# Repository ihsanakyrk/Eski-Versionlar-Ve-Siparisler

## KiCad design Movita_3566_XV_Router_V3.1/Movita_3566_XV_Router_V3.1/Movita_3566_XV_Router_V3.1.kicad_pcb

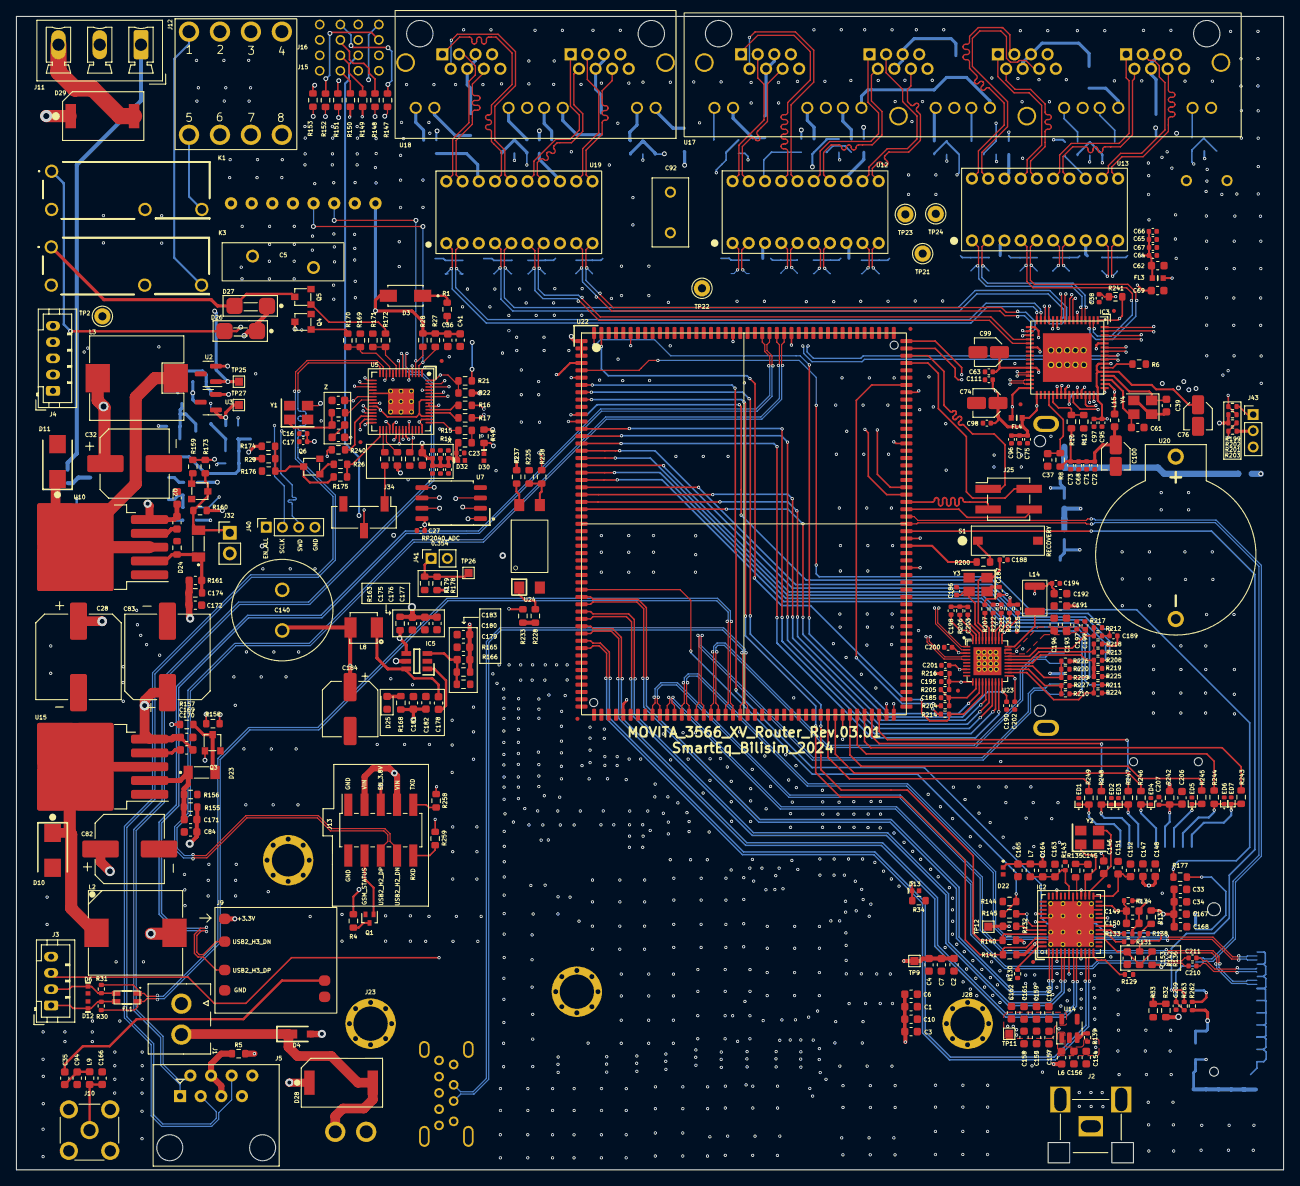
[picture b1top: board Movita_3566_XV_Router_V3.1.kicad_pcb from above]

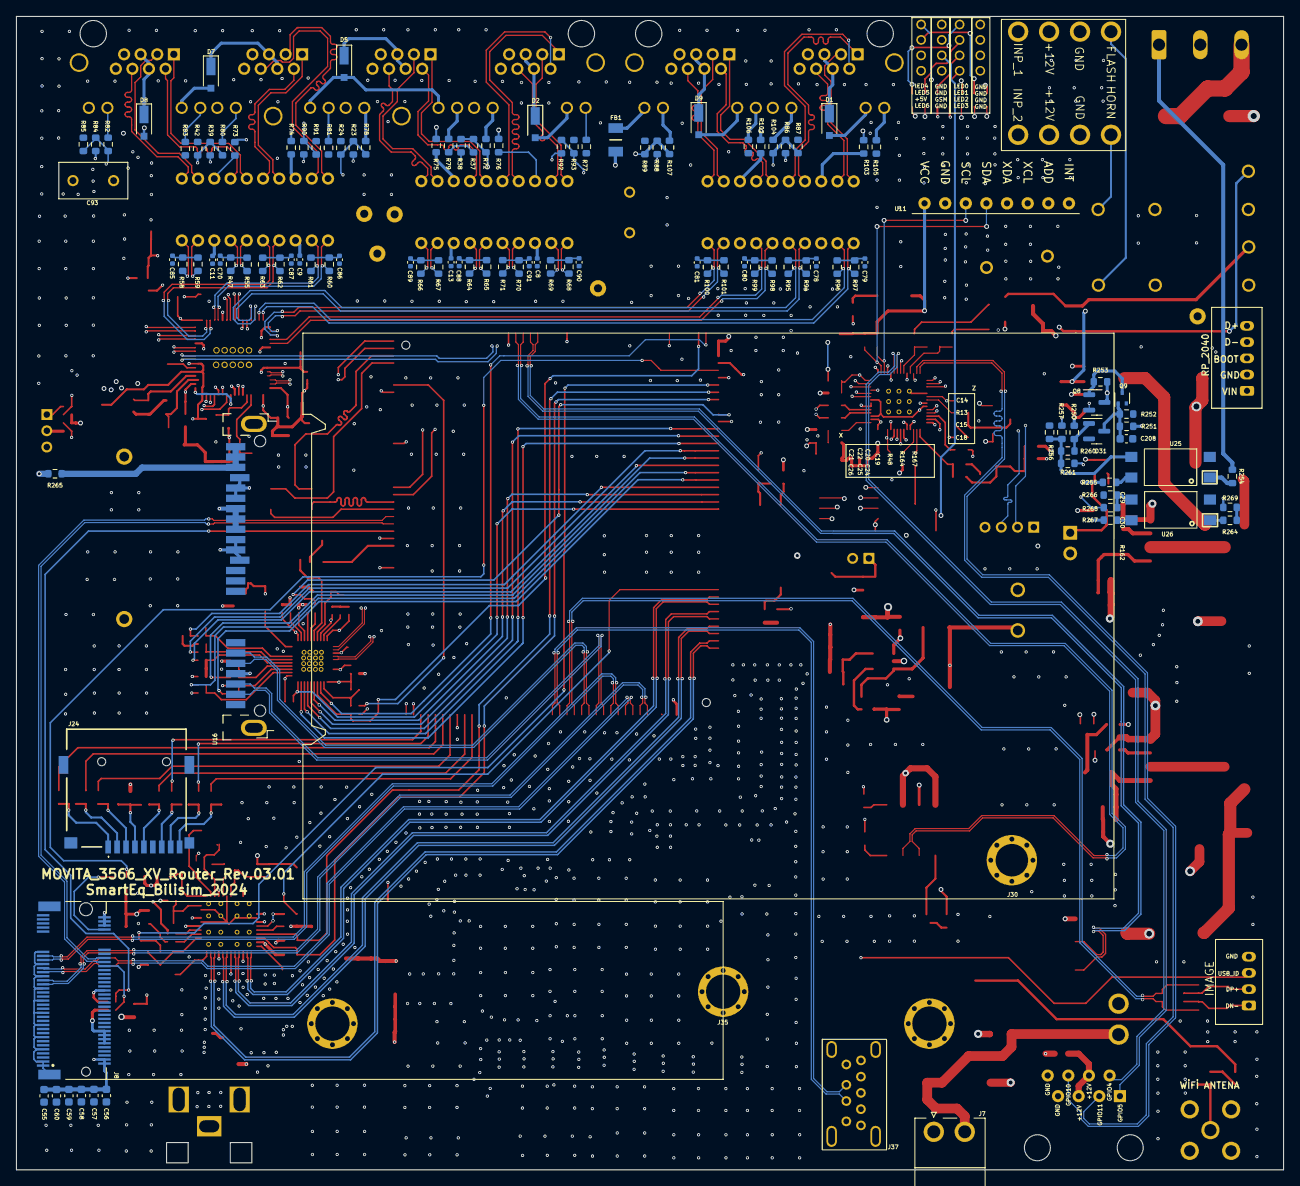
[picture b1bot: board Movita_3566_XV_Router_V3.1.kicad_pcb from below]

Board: 6 copper layers, 156.0 x 142.0 mm, 474 parts (118 on the bottom side), 347 nets.

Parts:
C1, C2, C3, C34, C36, C41, C55, C56, C57, C58, C59, C60, C147, C148, C150, C152, C156, C157, C158, C159, C160, C161, C162, C167, C168, C178, C182, C183, C208: 100nF; C_0603_1608Metric
C4, C6, C33, C149, C154, C191, C193, C196: 4.7uF; C_0603_1608Metric
C5: ERZ-V14D101; ERZV14D101
C7, C10, C37, C151, C155, C175, C176, C177, C192, C206: 10uF; C_0603_1608Metric
C8, C9, C11, C13, C16, C17, C20, C21, C22, C23, C24, C25, C26, C27, C38, C63, C64, C65, C66, C67, C68, C71, C72, C73, C75, C77, C95, C96, C97, C98, C111, C194, C195, C197, C198, C199, C200, C201, C202, C203, C207, C210, C211: 100nF; C_0402_1005Metric
C14, C15: 27pF; C_0603_1608Metric
C18, C19: 1uF; C_0603_1608Metric
C28, C83: 220uF/50V; C_Elec_10x10.2
C29, C30, C84, C169, C170, C172: 1uF/50V; C_0603_1608Metric
C32, C82: 330uF/25V; C_Elec_8x10.2
C35, C94, C166: 10pF; C_0603_1608Metric
C39, C61: 33pF; C_0603_1608Metric
C62, C69, C180, C181: 22uF; C_0603_1608Metric
C70, C78, C79, C80, C81, C85, C86, C87, C88, C89, C90, C91, C187, C189, C190: DNP; C_0402_1005Metric
C74, C76, C99, C100: 10uF; C_Elec_3x5.4
C92, C93: 1000PF 2KV; S102K33Y5PP63K5R
C140: 5.5V 0.22F; SuperCapacitor
C145, C146, C179: 22pF; C_0603_1608Metric
C153: 10nF; C_0603_1608Metric
C163: 100pF; C_0603_1608Metric
C164: DNP; C_0603_1608Metric
C165: 220pF; C_0603_1608Metric
C171, C174: 330nF; C_0603_1608Metric
C184: 220uF; CP_Elec_6.3x7.7
C185: 10nF; C_0402_1005Metric
C186, C188: 15pF; C_0402_1005Metric
C209: 100nF X7R 16V; C_0402_1005Metric
D1, D2, D4, D5, D7, D8, D9: 2SS100L-W; 2SS100LW
D3: SS14; DIOM4325X250N
D6, D12, D13, D30, D32: ESD5341N
D10, D11: SS54B
D22: ESD5451N
D23, D24: LL4148
D25: LED_GREEN; LED_0603_1608Metric
D26, D27: MRA4007T3G
D28, D29: S6MC
D31: BAT54; SOT-23
ED1, ED2, ED3, ED4, ED5, ED6, ED7: ESD5341N
FB1: YI321611U101-4R0T; BEADC3216X130N
FID1, FID2, FID5, FID6, FID7, FID8, FID9, FID10, FID11, FID12: DNP; Fiducial_0.5mm_Mask1mm
FL1: APCW3216-900P2T; DLW31SH222SQ2L
FL3, FL4: BLM18PG121SN1D; BLM18AG102BH1D
IC2: MS1836S_QFN48-7x7; QFN-48-1EP_7x7mm_P0.5mm_EP5.6x5.6mm
IC3: RTL8309N
IC5: SY8113B
J1: KF2EDGH-3.81-2P- Vertical; KF2EDGH-3.81-2P-Vertical
J2: DNP; AV_CON
J3: JST_PH_B4B-PH-K_1x04_P2.00mm_Vertical
J4: JST_PH_B5B-PH-K_1x05_P2.00mm_Vertical
J5: RJ45; RJ45_Amphenol_54602-x08_Horizontal
J7: KF2EDGH-3.81-2P- Right Angle; KF2EDGH-3.81-2P
J8: APCI0079-P002A J8900 M.2 M Key
J9: RTL8188EU
J10: SMA Connetor_inner_pin; SMA_Connector_inner_pin_right_angle
J11: KF2EDGR-Y-5.08-3P-Right Angle
J12: KF2EDGH-3.81_8P-Right Angle; KF2EDGH-3.81_8P
J13: MALE SMD Pin Header; PinSocket_2x05_P2.00mm_Vertical_SMD
J15, J16: LED_4_Block_Right Angle; LED_4_Block
J23, J28, J30: M3x*0.5 L=6; Screw Terminal Shinbo
J24: TF-CARD H1.8
J25: DNP; PinHeader_2x02_P2.54mm_Vertical_SMD
J32: DNP; PinHeader_1x02_P2.54mm_Vertical
J34: FEMALE SMD Pin Header; PinSocket_1x03_P2.54mm_Vertical_SMD_Pin1Left
J35: M3x*0.5 L=3; Screw Terminal Shinbo
J37: DNP; CP-USB-3015
J40: DNP; PinSocket_1x04_P2.00mm_Vertical
J41: DNP; PinSocket_1x02_P2.00mm_Vertical
J43: MALE Through Hole Pin Header; PinHeader_1x03_P2.00mm_Vertical
K1, K3: HF46F_5-HS1; HF46F5HS1
L2, L3: HX CYA1050-47UH; L_Bourns_SRR1208_12.7x12.7mm
L6: UPZ1608E101-3R0TF; L_0603_1608Metric
L7: MLI1608F-1R2KT; L_0603_1608Metric
L8: HA42-4R7MT; Inductor_0402_4.7uH
L9: SDCL1608C2N7STDF; L_0603_1608Metric
L14: AWL3225FP2R2MTF
L15: CBW160808U101T; L_0603_1608Metric
Q1: DTC043ZEBTL; SOT-416
Q2, Q3, Q4, Q5, Q6: MMBT2222ALT1G
Q8: DMG2305UX; SOT-23
Q9: DMG1012T; SOT-523
R1: 150R; R_0603_1608Metric
R4, R140, R141, R228, R264: 2.2K; R_0603_1608Metric
R5, R29, R241, R242: 0R; R_0603_1608Metric
R6, R8: 2.49K; R_0603_1608Metric
R10, R13, R21, R23, R37, R39, R48, R72, R77, R78, R79, R80, R81, R82, R83, R84, R87, R88, R104, R105, R106, R107, R132, R145, R170, R172, R233, R238, R250, R251, R257, R268, R269: 1K; R_0603_1608Metric
R12, R22, R24, R26, R38, R42, R47, R55, R58, R59, R60, R61, R62, R63, R64, R65, R66, R67, R68, R69, R70, R71, R85, R86, R89, R90, R91, R92, R93, R94, R95, R96, R97, R98, R99, R100, R101, R163, R167, R173, R174, R175, R176, R177, R240, R258, R259, R260, R261, R265: DNP; R_0603_1608Metric
R14: 200R; R_0603_1608Metric
R15: 1R; R_0603_1608Metric
R16, R17: 27R; R_0603_1608Metric
R27, R28, R32, R33, R34: 4.7K; R_0603_1608Metric
R30, R31: 2.2R; R_0402_1005Metric
R49, R136, R137, R149, R150, R155, R158, R159, R164, R169, R171, R235, R256, R266: 10K; R_0603_1608Metric
R73, R74, R75, R76, R102, R103: 75R; R_0603_1608Metric
R129, R138, R205, R225, R226: DNP; R_0402_1005Metric
R130, R199, R201, R262: 10K; R_0402_1005Metric
R131, R133, R134, R139, R204, R216: 0R; R_0402_1005Metric
R135: 330R; R_0603_1608Metric
R142, R243, R244, R245, R246, R247, R248, R249: 22R; R_0603_1608Metric
R143: 75R; R_0402_1005Metric
R144, R252, R253: 100K; R_0603_1608Metric
R147, R148, R151, R152, R153: 220R; R_0603_1608Metric
R156, R254: 3.3K; R_0603_1608Metric
R157, R160: 470R; R_0603_1608Metric
R161: 15K; R_0603_1608Metric
R162: 1.6K; R_0603_1608Metric
R165: 232K; R_0603_1608Metric
R166: 51K; R_0603_1608Metric
R168, R178: 2K; R_0603_1608Metric
R179: 180R; R_0603_1608Metric
R200: 100R; R_0603_1608Metric
R202, R203: 10R; R_0402_1005Metric
R206: 2.49K; R_0402_1005Metric
R207, R208, R209, R210, R211, R212, R213: 22R; R_0402_1005Metric
R214: 1.5K; R_0402_1005Metric
R215, R217, R218, R219, R220, R221, R222, R223, R224, R227: 4.7K; R_0402_1005Metric
R237, R255, R267: 33R; R_0603_1608Metric
R263: 1K; R_0402_1005Metric
S1: TS-1101-C-W
TP2, TP21, TP22, TP23, TP24: DNP; Pin_D1.0mm_L10.0mm
TP9, TP11, TP12, TP25, TP26, TP27: DNP; TestPoint_Pad_1.0x1.0mm
U2, U3: TLV76033DBZT; SOT-23
U5: RP2040; RP2040-QFN-56
U7: W25Q128JVSIQ; SOIC-8_5.23x5.23mm_P1.27mm
U10, U15: XL4015; TO-263-5_TabPin3
U11: DNP; module_mpu6050
U12, U13, U19: TF-218DG; RJ45_Transformer_2_Port
U14: RT9013-12GB; SOT-23-5
U16: SAF-8ASC-2132M; SATA_Connector_5622-1200-ML
U17: RJ45-4-Block; 4_Block_RJ45
U18: RJ45-2-Block; 2_Block_RJ45
U20: BS-2; BS-02-A1AJ010
U22: CM3566
U23: RTL8211F-CG
U24, U25, U26: PC817C; PC817
Y1: CF4012M00020001; Crystal_SMD_3225-4Pin_3.2x2.5mm
Y2: TAXM27M4RFBCCT2T; Crystal_SMD_3225-4Pin_3.2x2.5mm
Y3, Y4: X322525MSB4SI; Crystal_SMD_3225-4Pin_3.2x2.5mm

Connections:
3.3V_Sensor: C36.1, C41.1, D3.A, R27.1, R28.2, TP25.1, U2.1 (OUT), U11.1 (VCC)
+1V1: C16.1, C17.1, C18.1, U5.23 (DVDD), U5.45 (VREG_VOUT), U5.50 (DVDD)
/4 Port RJ45 and Transformer/+3.3V: C2.1, C4.1, C7.1, C55.1, C56.1, C57.1, C58.1, C59.1, C60.1, C140.1, C179.2, C180.2, C181.2, C182.2, C183.2, C184.1, C191.1, FB1.1, FL3.1, J8.2, J8.4, J8.12, J8.14, J8.16, J8.18, J8.70, J8.72, J8.74, J9.1, L6.1, L8.2, R29.2, R165.1, R168.1, R178.1, R199.1, R201.1, R216.1, R237.1, R242.2, R262.1, R267.1, TP9.1, U22.1, U22.2, U22.3
/4 Port RJ45 and Transformer/LED0: IC3.38 (P0LED/DIS_EEE), R37.1, R38.2, R72.1
/4 Port RJ45 and Transformer/LED1: IC3.39 (P1LED/LED_MODE[1]), R23.1, R24.2, R78.2
/4 Port RJ45 and Transformer/LED2: IC3.40 (P2LED/LED_MODE[2]), R39.1, R42.2, R80.2
/4 Port RJ45 and Transformer/LED3: IC3.42 (P3LED/RMAMODE), R82.2, R84.1, R85.2
/4 Port RJ45 and Transformer/LED4: IC3.43 (P4LED/UNKOWN_MULTI), R86.1, R87.2, R104.2
/4 Port RJ45 and Transformer/LED5: IC3.44 (P5LED/DIS_RST_BLNK), R88.1, R89.2, R107.2
/4 Port RJ45 and Transformer/RXI_0_N: IC3.57 (RXIN0), R71.2, U12.5
/4 Port RJ45 and Transformer/RXI_0_P: IC3.56 (RXIP0), R70.2, U12.4
/4 Port RJ45 and Transformer/RXI_1_N: IC3.63 (RXIN1), R64.2, U12.7
/4 Port RJ45 and Transformer/RXI_1_P: IC3.64 (RXIP1), R65.2, U12.6
/4 Port RJ45 and Transformer/RXI_2_N: IC3.3 (RXIN2), R63.2, U13.5
/4 Port RJ45 and Transformer/RXI_2_P: IC3.2 (RXIP2), R62.2, U13.4
/4 Port RJ45 and Transformer/RXI_3_N: IC3.9 (RXIN3), R47.2, U13.7
/4 Port RJ45 and Transformer/RXI_3_P: IC3.10 (RXIP3), R55.2, U13.6
/4 Port RJ45 and Transformer/RXI_4_N: IC3.14 (RXIN4), R95.2, U19.5
/4 Port RJ45 and Transformer/RXI_4_P: IC3.13 (RXIP4), R94.2, U19.4
/4 Port RJ45 and Transformer/RXI_5_N: IC3.20 (RXIN5), R99.2, U19.7
/4 Port RJ45 and Transformer/RXI_5_P: IC3.21 (RXIP5), R98.2, U19.6
/4 Port RJ45 and Transformer/TXO_0_N: IC3.58 (TXON0), R69.2, U12.2
/4 Port RJ45 and Transformer/TXO_0_P: IC3.59 (TXOP0), R68.2, U12.1
/4 Port RJ45 and Transformer/TXO_1_N: IC3.62 (TXON1), R66.2, U12.10
/4 Port RJ45 and Transformer/TXO_1_P: IC3.61 (TXOP1), R67.2, U12.9
/4 Port RJ45 and Transformer/TXO_2_N: IC3.4 (TXON2), R61.2, U13.2
/4 Port RJ45 and Transformer/TXO_2_P: IC3.5 (TXOP2), R60.2, U13.1
/4 Port RJ45 and Transformer/TXO_3_N: IC3.8 (TXON3), R58.2, U13.10
/4 Port RJ45 and Transformer/TXO_3_P: IC3.7 (TXOP3), R59.2, U13.9
/4 Port RJ45 and Transformer/TXO_4_N: IC3.15 (TXON4), R96.2, U19.2
/4 Port RJ45 and Transformer/TXO_4_P: IC3.16 (TXOP4), R97.2, U19.1
/4 Port RJ45 and Transformer/TXO_5_N: IC3.19 (TXON5), R100.2, U19.10
/4 Port RJ45 and Transformer/TXO_5_P: IC3.18 (TXOP5), R101.2, U19.9
/+12V: C32.1, C172.2, C174.2, C175.2, C176.2, C177.2, D1.2, D2.2, D4.2, D5.2, D7.2, D8.2, D9.2, IC5.5 (IN), J12.3, J12.7, L3.2, R5.1, R161.1, R163.1, R265.2, TP2.1, U17.P1_L_Led+, U17.P2_L_Led+, U17.P3_L_Led+, U17.P4_L_Led+, U18.P1_L_Led+, U18.P2_L_Led+
/CM3566/GMAC1_MCLKINOUT_M0: C187.1, R207.1, U22.11
/CM3566/GMAC1_MDC_M0: U22.186, U23.13 (MDC)
/CM3566/GMAC1_MDIO_M0: R214.2, U22.185, U23.14 (MDIO)
/CM3566/GMAC1_RXCLK_M0: C189.1, R212.1, U22.21
/CM3566/GMAC1_RXD0_M0: R208.1, U22.18
/CM3566/GMAC1_RXD1_M0: R209.1, U22.17
/CM3566/GMAC1_RXD2_M0: R210.1, U22.20
/CM3566/GMAC1_RXD3_M0: R211.1, U22.19
/CM3566/GMAC1_RXDV_CRS_M0: R213.1, U22.16
/CM3566/GMAC1_TXCLK_M0: C190.1, U22.24, U23.20 (TXC)
/CM3566/GMAC1_TXD0_M0: U22.13, U23.18 (TXD0)
/CM3566/GMAC1_TXD1_M0: U22.14, U23.17 (TXD1)
/CM3566/GMAC1_TXD2_M0: U22.22, U23.16 (TXD2)
/CM3566/GMAC1_TXD3_M0: U22.23, U23.15 (TXD3)
/CM3566/GMAC1_TXEN_M0: U22.15, U23.19 (TXCTL)
/CM3566/HDMI_TX_HPDIN: R144.1, R145.2, U22.35
/CM3566/LED0/CFG_EXT: R223.1, U23.32 (LED0/CFG_EXT)
/CM3566/LED1/CFG_LDO0: R221.2, U23.33 (LED1/CFG_LDO0_)
/CM3566/LED2/CFG_LDO1: R222.2, U23.34 (LED2/CFG_LDO1)
/CM3566/PCIE20_CLKREQn_M2: J8.52, U22.120
/CM3566/PCIE20_PERSTn_M2: R263.1, U22.118
/CM3566/PCIE20_REFCLKN: J8.53, U22.65
/CM3566/PCIE20_REFCLKP: J8.55, U22.64
/CM3566/PCIE20_RXN: J8.41, U22.61
/CM3566/PCIE20_RXP: J8.43, U22.60
/CM3566/PCIE20_TXN: C210.1, U22.62
/CM3566/PCIE20_TXP: C211.1, U22.63
/CM3566/PCIE20_WAKEn_M2: J8.54, U22.119
/CM3566/PHY0_XTALIN: C188.1, U23.36 (XTAL_IN), Y3.1 (XIN)
/CM3566/PHY0_XTALOUT: C186.1, U23.37 (XTAL_OUT/EXT_CLK), Y3.3 (XOUT)
/CM3566/PHY1_MDI0+: IC3.28 (TXOP7), U23.1 (MDI[0]+)
/CM3566/PHY1_MDI0-: IC3.29 (TXON7), U23.2 (MDI[0]-)
/CM3566/PHY1_MDI1+: IC3.31 (RXIP7), U23.4 (MDI[1]+)
/CM3566/PHY1_MDI1-: IC3.30 (RXIN7), U23.5 (MDI[1]-)
/CM3566/PHY-Reset: C185.1, R204.2, R205.1, U23.12 (PHYRSTB)
/CM3566/PHY_CLKOUT125: R207.2, U23.35 (CLKOUT)
/CM3566/PHY_RXCLK/PHYAD1: R212.2, R217.2, U23.27 (RXC/PHYAD1)
/CM3566/PHY_RXD0/RXDLY: R208.2, R219.2, R225.1, U23.25 (RXD0/RXDLY)
/CM3566/PHY_RXD1/TXDLY: R209.2, R220.2, R226.1, U23.24 (RXD1/TXDLY)
/CM3566/PHY_RXD2/PLLOFF: R210.2, R227.1, U23.23 (RXD2/PLLOFF)
/CM3566/PHY_RXD3/PHYAD0: R211.2, R224.1, U23.22 (RXD3/PHYAD0)
/CM3566/PHY_RXDV/PHYAD2: R213.2, R218.2, U23.26 (RXCTL/PHYAD2)
/CM3566/PMIC_32KOUT_SOC: R177.1, U22.5
/CM3566/REG_OUT: L14.1, U23.30 (REG_OUT)
/CM3566/RSET: R206.2, U23.39 (RSET)
/CM3566/SARADC_VIN0_KEY/RECOVERY: R200.1, U22.116
/CM3566/SATA0_RXN: U16.S5 (RX-), U22.69
/CM3566/SATA0_RXP: U16.S6 (RX+), U22.68
/CM3566/SATA0_TXN: U16.S3 (TX-), U22.67
/CM3566/SATA0_TXP: U16.S2 (TX+), U22.66
/CM3566/SDMMC0_CLK: R246.1, U22.85
/CM3566/SDMMC0_CMD: R245.1, U22.87
/CM3566/SDMMC0_D0: R247.1, U22.91
/CM3566/SDMMC0_D1: R248.1, U22.90
/CM3566/SDMMC0_D2: R243.1, U22.89
/CM3566/SDMMC0_D3: R244.1, U22.88
/CM3566/SDMMC0_DET_L: R249.1, U22.84
/CM3566/SPI3_CLK_M1: R204.1, U22.138
/CM3566/SPI3_MOSI_M1: R215.1, U22.137, U23.31 (INTB/PMEB)
/CM3566/UART2_RX_M0_DEBUG: R201.2, R203.2, U22.143
/CM3566/UART2_TX_M0_DEBUG: R199.2, R202.2, U22.144
/CM3566/UART3_RX_M0: J25.4, U22.121
/CM3566/UART3_TX_M0: J25.3, U22.122
/CM3566/UART4_RX_M0: R259.2, U5.27 (GPIO16), U22.123
/CM3566/UART4_TX_M0: R258.2, U5.28 (GPIO17), U22.124
/CM3566/UART5_RX_M1: J25.2, U22.141
/CM3566/UART5_TX_M1: J25.1, U22.142
/CM3566/USB2_HOST2_DN: J13.8, U22.160
/CM3566/USB2_HOST2_DP: J13.6, U22.161
/CM3566/USB2_HOST3_DN: J9.2, U22.163
/CM3566/USB2_HOST3_DP: J9.3, U22.162
/CM3566/USB3_HOST1_DN: J37.2 (D-), U22.73
/CM3566/USB3_HOST1_DP: J37.3 (D+), U22.72
/CM3566/USB3_OTG0_DN: FL1.4, R30.1, U22.70
/CM3566/USB3_OTG0_DP: FL1.1, R31.1, U22.71
/CM3566/USB3_OTG0_ID: D13.1, J3.3, R34.2, U22.92
/CM3566/USB3_OTG0_VBUSDET: R32.2, R33.1, U22.93
/CM3566/VCC3V3_LAN: C193.1, C195.1, C196.1, C197.1, C198.1, C199.1, R205.2, R214.1, R215.2, R216.2, R223.2, R224.2, R225.2, R226.2, R227.2, U23.11 (AVDD33_2), U23.28 (DVDD_RG), U23.29 (DVDD33), U23.40 (AVDD33_1)
/CM3566/VDD10_EPHY: C192.1, C194.1, C200.1, C201.1, C202.1, C203.1, L14.2, U23.3 (AVDD10_3), U23.8 (AVDD10_2), U23.21 (DVDD10), U23.38 (AVDD10_1)
/CM3566/VDD_5V: C1.1, C3.1, C6.1, C10.1, C82.1, C84.2, C171.2, D26.1 (K), D27.1 (K), J16.6, J37.1 (VBUS), K1.2 (COIL_2), K3.2 (COIL_2), L2.2, R32.1, R155.1, R174.2, U16.P7 (VCC5), U16.P8 (VCC5), U16.P9 (VCC5)
/CM3566/VRTC: R1.2, U20.1 (+), U22.4
/EC25_Sim/GSM_LED: J16.5, R4.2
/EC25_Sim/GSM_STATUS: J13.4, Q1.1 (B)
/HDMI_CVBS/CVideo_OUT: C164.2, C165.1, D22.1, J2.1, J2.2, L7.2
/HDMI_CVBS/DAC_R: C163.1, C164.1, IC2.31 (AV_OUT), L7.1, R143.2
/HDMI_CVBS/HDMITX_CEC_M0: R142.1, U22.7
/HDMI_CVBS/HDMI_RX_HPD: IC2.43 (HDMIRX_HPD), R145.1
/HDMI_CVBS/HDMI_TX0N_PORT: IC2.4 (HDMI_RX0N), U22.38
/HDMI_CVBS/HDMI_TX0P_PORT: IC2.5 (HDMI_RX0P), U22.39
/HDMI_CVBS/HDMI_TX1N_PORT: IC2.7 (HDMI_RX1N), U22.40
/HDMI_CVBS/HDMI_TX1P_PORT: IC2.8 (HDMI_RX1P), U22.41
/HDMI_CVBS/HDMI_TX2N_PORT: IC2.10 (HDMI_RX2N), U22.42
/HDMI_CVBS/HDMI_TX2P_PORT: IC2.11 (HDMI_RX2P), U22.43
/HDMI_CVBS/HDMI_TXCLKN_PORT: IC2.1 (HDMI_RXCN), U22.36
/HDMI_CVBS/HDMI_TXCLKP_PORT: IC2.2 (HDMI_RXCP), U22.37
/HDMI_CVBS/P/N_SEL: R131.1, R137.2, R138.1
/HDMI_CVBS/RSTn: C153.1, IC2.15 (RSTn), R136.1, R142.2
/HDMI_CVBS/RXDDC_SCL: IC2.46 (RXDDC_SCL), R141.1, U22.9
/HDMI_CVBS/RXDDC_SDA: IC2.45 (RXDDC_SDA), R140.1, U22.8
/HDMI_CVBS/RX_DET: IC2.44 (HDMIRX_DET), R132.2
/HDMI_CVBS/VDD10_EPHY: C155.1, C157.1, C158.1, C159.1, C160.1, C161.1, C162.1, IC2.3 (AVDD12), IC2.9 (AVDD12_1), IC2.20 (DVDD12), IC2.40 (DVDD12_1), TP11.1, U14.5 (OUT)
/HDMI_CVBS/XTAL1: C145.1, IC2.27 (XTOUT), Y2.1
/HDMI_CVBS/XTAL2: C146.1, IC2.26 (XTIN), Y2.3
/IO Connector/FLASH: J12.1, K3.4 (COM)
/IO Connector/GP3_A: J34.1, R167.2
/IO Connector/HORN: J12.5, K1.4 (COM)
/IO Connector/SWCLK: J40.2, U5.24 (SWCLK)
/IO Connector/SWD: J40.3, U5.25 (SWD)
/Power Unit/+3V3_Mini: C19.1, C20.1, C21.1, C22.1, C23.1, C24.1, C25.1, C26.1, C27.1, D32.1, Q8.2 (S), R14.1, R22.1, R157.1, R160.1, U5.1 (IOVDD), U5.10 (IOVDD), U5.22 (IOVDD), U5.33 (IOVDD), U5.42 (IOVDD), U5.44 (VREG_IN), U5.48 (USB_VDD), U5.49 (IOVDD), U7.8 (VCC)
/Power Unit/IGN_LOGIC: R256.1, R257.1, R260.1, R261.1, U25.3 (E)
/Power Unit/IGN_V: Q8.3 (D), R250.2, R253.2, R255.1, TP27.1, U3.1 (OUT)
/Power Unit/MCU_Power_EN: Q6.3 (C), R29.1, R174.1, R175.1, R176.1
/RP2040/GPIO0: R27.2, U5.2 (GPIO0), U11.4 (SDA)
/RP2040/GPIO1: R28.1, U5.3 (GPIO1), U11.3 (SCL)
/RP2040/GPIO2: R251.1, R261.2, U5.4 (GPIO2)
/RP2040/GPIO3: R257.2, U5.5 (GPIO3)
/RP2040/GPIO4: J5.2, U5.6 (GPIO4)
/RP2040/GPIO5: J5.1, U5.7 (GPIO5)
/RP2040/GPIO6: R147.1, U5.8 (GPIO6)
/RP2040/GPIO7: R171.1, R172.1, U5.9 (GPIO7)
/RP2040/GPIO8: R169.1, R170.1, U5.11 (GPIO8)
/RP2040/GPIO9: R148.1, U5.12 (GPIO9)
/RP2040/GPIO10: J5.6, U5.13 (GPIO10)
/RP2040/GPIO11: J5.3, U5.14 (GPIO11)
/RP2040/GPIO12: R151.1, U5.15 (GPIO12)
/RP2040/GPIO13: R152.1, U5.16 (GPIO13)
/RP2040/GPIO14: R153.1, U5.17 (GPIO14)
/RP2040/GPIO18: R26.1, R175.2, U5.29 (GPIO18)
/RP2040/GPIO19: R167.1, U5.30 (GPIO19)
/RP2040/GPIO20: R164.2, U5.31 (GPIO20)
/RP2040/GPIO21: J13.5, U5.32 (GPIO21)
/RP2040/GPIO22: R158.1, U5.34 (GPIO22)
/RP2040/GPIO23: R159.1, R173.1, U5.35 (GPIO23)
/RP2040/GPIO24: R268.2, U5.36 (GPIO24)
/RP2040/GPIO25: R238.2, U5.37 (GPIO25)
/RP2040/GPIO26_ADC0: J41.1, R178.2, R179.1, TP26.1, U5.38 (GPIO26_ADC0)
/RP2040/GPIO27_ADC1: D30.1, R48.1, R49.2, U5.39 (GPIO27_ADC1)
/RP2040/QSPI_SCLK: U5.52 (QSPI_SCLK), U7.6 (CLK)
/RP2040/QSPI_SD0: U5.53 (QSPI_SD0), U7.5 (DI(IO0))
/RP2040/QSPI_SD1: U5.55 (QSPI_SD1), U7.2 (DO(IO1))
/RP2040/QSPI_SD2: U5.54 (QSPI_SD2), U7.3 (IO2)
/RP2040/QSPI_SD3: U5.51 (QSPI_SD3), U7.7 (IO3)
/RP2040/QSPI_SS: R21.1, R22.2, U5.56 (QSPI_SS), U7.1 (~CS)
/RP2040/RUN: J34.2, R240.2
/RP2040/USB_D+_RP2040: J4.5, R16.1
/RP2040/USB_D-_RP2040: J4.4, R17.1
/RP2040/USB_D_N: R17.2, U5.46 (USB_DM)
/RP2040/USB_D_P: R16.2, U5.47 (USB_DP)
/RP2040/XIN: C14.1, U5.20 (XIN), Y1.3
/RP2040/XOUT: R13.1, U5.21 (XOUT)
/RP2040/~USB_BOOT: J4.3, R21.2
/RTL8309E/1V0_AVDD: C76.1, C95.1, C97.1, FL4.1, IC3.1 (AVDDL_1), IC3.12 (AVDDL_2), IC3.22 (AVDDL_3), IC3.32 (AVDDL_4), IC3.48 (V10OUT), IC3.53 (AVDDLPLL), IC3.55 (AVDDL_5), R241.2, TP24.1
/RTL8309E/1V0_DVDD: C74.1, C75.1, C77.1, C96.1, C98.1, C111.1, FL4.2, IC3.33 (DVDDL_2), IC3.47 (DVDDL_3), TP23.1
/RTL8309E/ETH_DVDD3V3: C68.1, C69.1, C71.1, C72.1, C73.1, C100.1, IC3.6 (AVDDH_1), IC3.41 (DVDDH), IC3.49 (V33IN), L15.2, R8.1, R10.2, R23.2, R37.2, R39.2, R84.2, R86.2, R88.2, R90.2, R92.2, TP22.1
/RTL8309E/LED6: IC3.45 (P6LED), R90.1, R91.2
/RTL8309E/LED7: IC3.46 (P7LED), R92.1, R93.2
ADC_VREF: R14.2, R15.1
CMT1: R76.2, U12.18
CMT2: R75.2, U12.13
CMT3: R74.2, U13.18
CMT4: R73.2, U13.13
CMT5: R103.2, U19.18
CMT6: R102.2, U19.13
CT: C8.1, C9.1, C11.1, C13.1, C62.1, C63.1, C64.1, C65.1, C66.1, C67.1, C99.1, FL3.2, IC3.17 (AVDDH_2), IC3.27 (AVDDH_3), IC3.50 (AVDDHPLL), IC3.60 (AVDDH_4), L15.1, TP21.1, U12.3, U12.8, U13.3, U13.8, U19.3, U19.8
Earth: C1.2, C2.2, C3.2, C4.2, C5.2, C6.2, C7.2, C8.2, C9.2, C10.2, C11.2, C13.2, C14.2, C15.2, C16.2, C17.2, C18.2, C19.2, C20.2, C21.2, C22.2, C23.2, C24.2, C25.2, C26.2, C27.2, C28.2, C29.1, C32.2, C33.2, C34.2, C36.2, C37.2, C38.2, C39.2, C41.2, C55.2, C56.2, C57.2, C58.2, C59.2, C60.2, C61.2, C62.2, C63.2, C64.2, C65.2, C66.2, C67.2, C68.2, C69.2, C70.2, C71.2, C72.2, C73.2, C74.2, C75.2, C76.2, C77.2, C78.2, C79.2, C80.2, C81.2, C82.2, C83.2, C84.1, C85.2, C86.2, C87.2, C88.2, C89.2, C90.2, C91.2, C92.1, C94.2, C95.2, C96.2, C97.2, C98.2, C99.2, C100.2, C111.2, C140.2, C145.2, C146.2, C147.2, C148.2, C149.2, C150.2, C151.2, C152.2, C153.2, C154.2, C155.2, C156.2, C157.2, C158.2, C159.2, C160.2, C161.2, C162.2, C163.2, C165.2, C166.2, C167.2, C168.2, C169.1, C172.1, C175.1, C176.1, C177.1, C180.1, C181.1, C182.1, C183.1, C184.2, C185.2, C186.2, C187.2, C188.2, C189.2, C190.2, C191.2, C192.2, C193.2, C194.2, C195.2, C196.2, C197.2, C198.2, C199.2, C200.2, C201.2, C202.2, C203.2, C206.2, C207.2, C208.1, C209.2, D6.2, D10.2, D11.2, D12.2, D13.2, D22.2, D25.1 (K), D30.2, D32.2, ED1.2, ED2.2, ED3.2, ED4.2, ED5.2, ED6.2, ED7.2, IC2.19 (VSS), IC2.22 (VREF_L), IC2.30 (VSS_1), IC2.41 (VSS_2), IC2.49 (GND(EPAD)), IC3.65 (EP), IC5.2 (GND), J1.1, J2.3, J3.4, J4.2, J5.7, J5.8, J7.1, J8.1, J8.3, J8.9, J8.15, J8.21, J8.27, J8.33, J8.39, J8.45, J8.51, J8.57, J8.71, J8.73, J8.75, J8.SH1 (SHIELD), J8.SH2 (SHIELD), J9.4, J9.5, J10.2, J10.3, J10.4, J10.5, J11.2, J12.2, J12.6, J13.1, J13.2, J15.1, J15.3, J15.5, J15.7, J16.1, J16.3, J16.7, J23.1, J24.6 (VSS), J24.10 (G1), J24.11 (G2), J24.12 (G3), J24.13 (G4), J28.1, J30.1, J32.2, J34.3, J35.1, J37.4 (GND), J37.7 (DRAIN), J37.10 (SHIELD), J40.4, J41.2, J43.3, Q1.2 (E), Q2.2 (E), Q3.2 (E), Q4.2 (E), Q5.2 (E), Q6.2 (E), Q9.2 (S), R6.2, R12.1, R24.1, R33.2, R38.1, R42.1, R48.2, R77.2, R79.2, R81.2, R83.2, R85.1, R87.1, R89.1, R91.1, R93.1, R105.2, R106.2, R129.1, R130.1, R133.1, R135.1, R138.2, R143.1, R144.2, R156.2, R162.2, R166.2, R169.2, R171.2, R176.2, R179.2, R206.1, R217.1, R218.1, R219.1, R220.1, R221.1, R222.1, R235.1, R252.1, R256.2, R266.1, S1.2, U2.3 (GND), U3.3 (GND), U5.19 (TESTEN), U5.57 (GND), U7.4 (GND), U10.1 (GND), U11.2 (GND), U14.2 (GND), U15.1 (GND), U16.GND, U16.P4 (GND), U16.P5 (GND), U16.P6 (GND), U16.P10 (GND), U16.P11 (GND), U16.P12 (GND), U16.S1 (GND), U16.S4 (GND), U16.S7 (GND), U17.7_1, U17.7_2, U17.7_3, U17.7_4, U17.8_1, U17.8_2, U17.8_3, U17.8_4, U18.7_1, U18.7_2, U18.8_1, U18.8_2, U20.2 (-), U22.6, U22.12, U22.56, U22.86, U22.113, U22.117, U22.130, U22.159, U22.167, U22.181, U23.41 (E_Pad), U24.2 (K), U25.2 (K), U26.2 (K), Y1.2, Y1.4, Y2.2, Y2.4, Y3.2 (GND), Y3.4 (GND), Y4.2, Y4.4
GNDPWR: C92.2, C93.2, U17.SHIELD, U18.SHIELD
IGN: J11.1, R149.1, R254.2
LED_VDD: FB1.2, U17.P1_R_Led+, U17.P2_R_Led+, U17.P3_R_Led+, U17.P4_R_Led+, U18.P1_R_Led+, U18.P2_R_Led+
LIND_DS_LED: IC3.37 (LDIND/DIS_LD), R10.1, R12.2
unnamed: C15.1, R13.2, Y1.1
unnamed: C35.1, C94.1, L9.1
unnamed: C70.1, R47.1, R55.1
unnamed: C78.1, R94.1, R95.1
unnamed: C79.1, R96.1, R97.1
unnamed: C80.1, R98.1, R99.1
unnamed: C81.1, R100.1, R101.1
unnamed: C85.1, R58.1, R59.1
unnamed: C86.1, R60.1, R61.1
unnamed: C87.1, R62.1, R63.1
unnamed: C88.1, R64.1, R65.1
unnamed: C89.1, R66.1, R67.1
unnamed: C90.1, R68.1, R69.1
unnamed: C91.1, R70.1, R71.1
unnamed: C93.1, R73.1, R74.1, R75.1, R76.1, R102.1, R103.1
unnamed: D3.C, R1.1
unnamed: D25.2 (A), R168.2
unnamed: D26.2 (A), K1.1 (COIL_1), Q4.3 (C)
unnamed: D27.2 (A), K3.1 (COIL_1), Q5.3 (C)
unnamed: D31.1, R250.1, R260.2
unnamed: IC2.29 (DAC_REF), R135.2
unnamed: IC2.16 (KEY0), R131.2
unnamed: IC2.17 (KEY1), R133.2
unnamed: IC2.12 (MCU_SEL), R129.2
unnamed: IC2.48 (REXT), R130.2
unnamed: C151.1, C152.1, IC2.25 (VMID)
unnamed: C149.1, C150.1, IC2.23 (VREF_H), R134.1
unnamed: C38.1, IC3.11 (DVDDL_1), R241.1
unnamed: IC3.54 (IBREF), R6.1
unnamed: C37.1, IC3.36 (RESETB), R8.2
unnamed: C178.1, IC5.1 (BS)
unnamed: IC5.4 (EN), R163.2, R164.1
unnamed: C179.1, IC5.3 (FB), R165.2, R166.1
unnamed: C178.2, IC5.6 (LX), L8.1
unnamed: D4.1, D28.2, J1.2, J7.2
unnamed: D12.1, FL1.3, J3.1, R30.2
unnamed: D6.1, FL1.2, J3.2, R31.2
unnamed: J5.4, J5.5, R5.2
unnamed: J8.38, R262.2
unnamed: C210.2, J8.47
unnamed: C211.2, J8.49
unnamed: C209.1, J8.50, R263.2
unnamed: J8.68, R177.2
unnamed: C35.2, J9.6
unnamed: C166.1, J10.1, L9.2
unnamed: J12.4, R269.1
unnamed: J12.8, R233.1
unnamed: J13.9, R258.1
unnamed: J13.10, R259.1
unnamed: J15.2, R147.2
unnamed: J15.4, R148.2
unnamed: J15.6, R149.2
unnamed: J15.8, R150.2
unnamed: J16.2, R151.2
unnamed: J16.4, R152.2
unnamed: J16.8, R153.2
unnamed: ED1.1, J24.9 (CD), R249.2
unnamed: ED6.1, J24.2 (CD/DAT3), R244.2
unnamed: ED4.1, J24.5 (CLK), R246.2
unnamed: ED5.1, J24.3 (CMD), R245.2
unnamed: ED3.1, J24.7 (DAT0), R247.2
unnamed: ED2.1, J24.8 (DAT1), R248.2
unnamed: ED7.1, J24.1 (DAT2), R243.2
unnamed: C206.1, C207.1, J24.4 (VDD), R242.1
unnamed: D24.2, J32.1, Q2.3 (C), R160.2, R173.2
unnamed: J43.1, R202.1
unnamed: J43.2, R203.1
unnamed: Q1.3 (C), R4.1
unnamed: Q2.1 (B), R159.2
unnamed: Q3.1 (B), R158.2
unnamed: D23.2, Q3.3 (C), R157.2
unnamed: Q4.1 (B), R170.2
unnamed: Q5.1 (B), R172.2
unnamed: Q6.1 (B), R26.2
unnamed: Q8.1 (G), Q9.3 (D), R253.1
unnamed: C208.2, D31.3, Q9.1 (G), R251.2, R252.2
unnamed: R72.2, U17.P1_R_Led-
unnamed: R77.1, U17.P1_L_Led-
unnamed: R78.1, U17.P2_R_Led-
unnamed: R79.1, U17.P2_L_Led-
unnamed: R80.1, U17.P3_R_Led-
unnamed: R81.1, U17.P3_L_Led-
unnamed: R82.1, U17.P4_R_Led-
unnamed: R83.1, U17.P4_L_Led-
unnamed: R104.1, U18.P1_R_Led-
unnamed: R105.1, U18.P1_L_Led-
unnamed: R106.1, U18.P2_L_Led-
unnamed: R107.1, U18.P2_R_Led-
unnamed: R200.2, S1.1
unnamed: R228.1, R233.2
unnamed: R264.1, R269.2
unnamed: R265.1, U16.P13 (VCC12), U16.P14 (VCC12), U16.P15 (VCC12)
unnamed: R15.2, U5.43 (ADC_AVDD)
unnamed: R240.1, U5.26 (RUN)
unnamed: C174.1, D24.1, R161.2, R162.1, U10.2 (FB)
unnamed: D11.1, L3.1, U10.3 (SW)
unnamed: C30.1, U10.4 (VC)
unnamed: R139.2, U14.3 (EN)
unnamed: C171.1, D23.1, R155.2, R156.1, U15.2 (FB)
unnamed: D10.1, L2.1, U15.3 (SW)
unnamed: C170.1, U15.4 (VC)
unnamed: D2.1, U17.4_1, U17.5_1
unnamed: D5.1, U17.4_2, U17.5_2
unnamed: D7.1, U17.4_3, U17.5_3
unnamed: D8.1, U17.4_4, U17.5_4
unnamed: D1.1, U18.4_1, U18.5_1
unnamed: D9.1, U18.4_2, U18.5_2
unnamed: R228.2, U24.1 (A)
unnamed: R237.2, U24.4 (C)
unnamed: R235.2, R238.1, U24.3 (E)
unnamed: R254.1, U25.1 (A)
unnamed: R255.2, U25.4 (C)
unnamed: R264.2, U26.1 (A)
unnamed: R267.2, U26.4 (C)
unnamed: R266.2, R268.1, U26.3 (E)
RX0_N: U12.16, U17.2_1
RX0_P: U12.17, U17.1_1
RX1_N: U12.14, U17.2_2
RX1_P: U12.15, U17.1_2
RX2_N: U13.16, U17.2_3
RX2_P: U13.17, U17.1_3
RX3_N: U13.14, U17.2_4
RX3_P: U13.15, U17.1_4
RX4_N: U18.2_1, U19.16
RX4_P: U18.1_1, U19.17
RX5_N: U18.2_2, U19.14
RX5_P: U18.1_2, U19.15
TX0_N: U12.19, U17.6_1
TX0_P: U12.20, U17.3_1
TX1_N: U12.11, U17.6_2
TX1_P: U12.12, U17.3_2
TX2_N: U13.19, U17.6_3
TX2_P: U13.20, U17.3_3
TX3_N: U13.11, U17.6_4
TX3_P: U13.12, U17.3_4
TX4_N: U18.6_1, U19.19
TX4_P: U18.3_1, U19.20
TX5_N: U18.6_2, U19.11
TX5_P: U18.3_2, U19.12
VCC_3V3_S0: C33.1, C34.1, C147.1, C148.1, C154.1, C156.1, C167.1, C168.1, IC2.6 (AVDD33), IC2.18 (DVDD33), IC2.28 (AVDD33_1), IC2.34 (AVDD33_2), IC2.42 (DVDD33_1), IC2.47 (AVDD33_3), L6.2, R132.1, R134.2, R136.2, R137.1, R139.1, R140.2, R141.2, TP12.1, U14.1 (IN)
VIN: C5.1, C28.1, C29.2, C30.2, C83.1, C169.2, C170.2, D28.1, D29.1, J4.1, J13.3, J13.7, K1.3 (NO), K3.3 (NO), R49.1, R150.1, U2.2 (IN), U3.2 (IN), U10.5 (VIN), U15.5 (VIN)
VRAW: D29.2, J11.3
XI: C39.1, IC3.52 (XI), Y4.1
XO: C61.1, IC3.51 (XO), Y4.3
